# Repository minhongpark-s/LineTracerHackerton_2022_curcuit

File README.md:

# LineTracerHackerton_2022_curcuit
하이멕 2022 라트톤 회로(기판)설계입니다.

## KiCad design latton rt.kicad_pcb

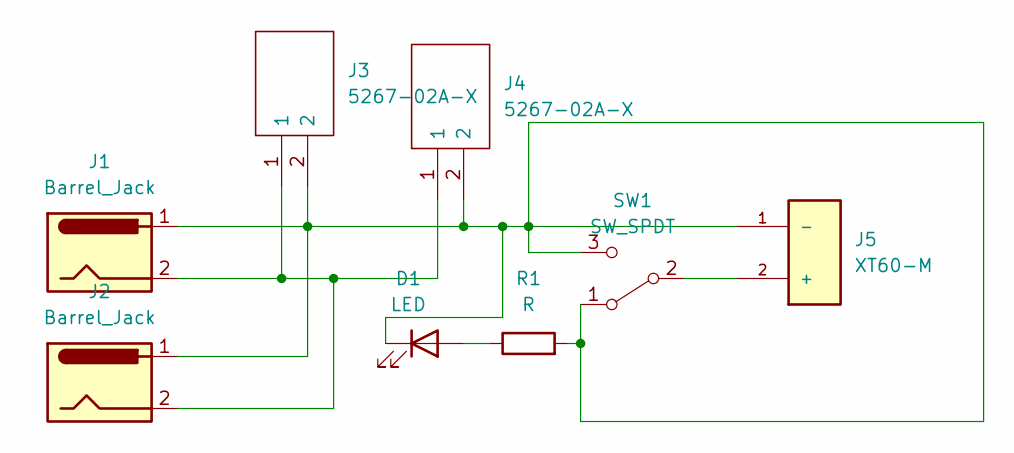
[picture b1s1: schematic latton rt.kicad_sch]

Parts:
D1: LED; LED_0603_1608Metric; LCSC Part # C2286
J1, J2: Barrel_Jack; BarrelJack_Horizontal
J3, J4: 5267-02A-X; Molex_SPOX_5267-02A_1x02_P2.50mm_Vertical; Manufacturer_Part_Number 5267-02A-X
J5: XT60-M; AMASS_XT60-M; PARTREV 1.2
R1: R; R_0805_2012Metric; LCSC Part # C17617
SW1: SW_SPDT; SW_CuK_JS202011AQN_DPDT_Angled

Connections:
unnamed: D1.2 (A), R1.1
unnamed: D1.1 (K), J1.1, J2.1, J3.2, J4.2, J5.1 (-), R1.2, SW1.1 (A), SW1.3 (C)
unnamed: J1.2, J2.2, J3.1, J4.1
unnamed: J5.2 (+), SW1.2 (B)

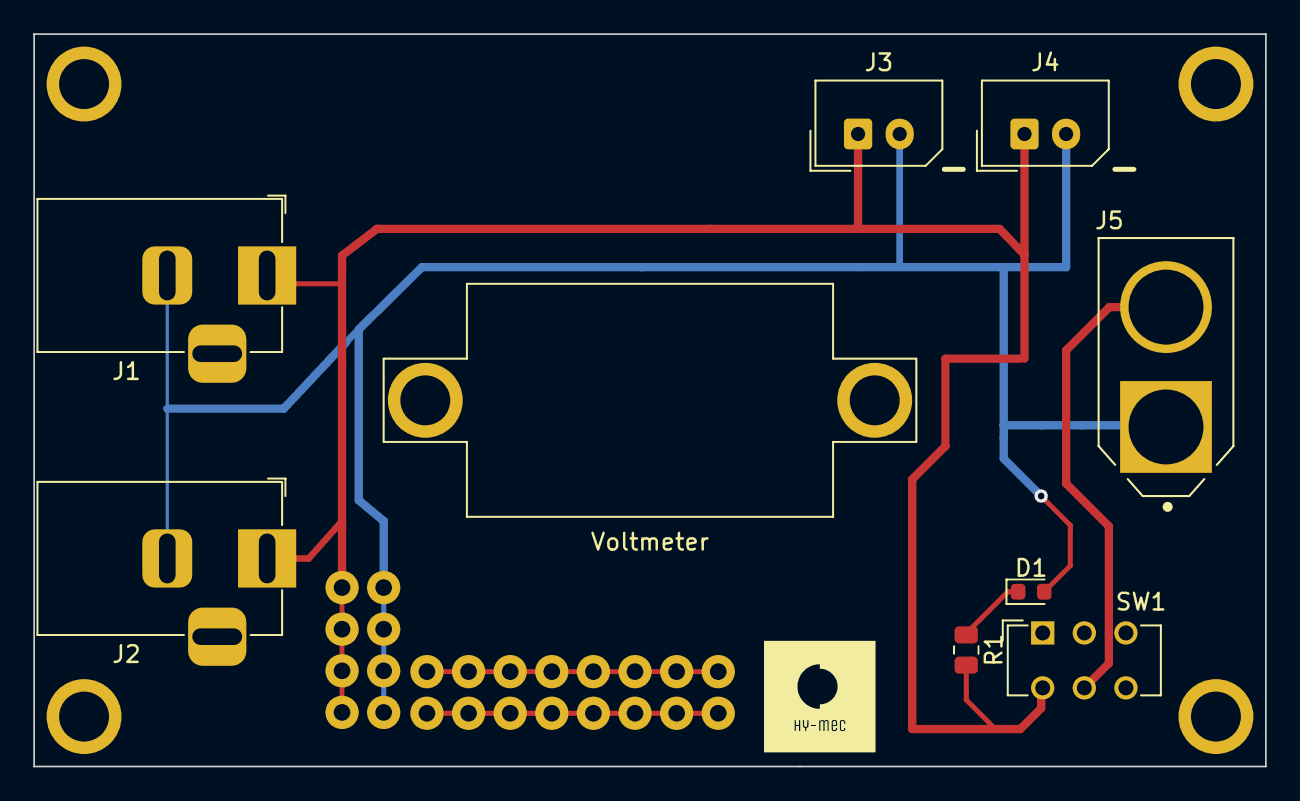
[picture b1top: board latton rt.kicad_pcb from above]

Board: 2 copper layers, 74.0 x 44.0 mm, 9 parts (0 on the bottom side), 4 nets.

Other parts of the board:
Voltmeter: PIN_Wls

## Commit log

2022-03-04 22/03/05 1:58
